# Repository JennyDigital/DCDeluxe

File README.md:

## It's a door chime board, but programmable.

It can literally sound however you want, but the source-code (unfinished) is provided to get you up-and-runninng.

Have you wondered why there's four DIP switches?.. Coming soon:  A melody playing feature!

...also, let me apologise for the ugly appearance of the CubeMX generated portions of the code, the tool generates ugly code and re-generates it with each re-generated change.  You can tidy it, but it'll just go back to ugly each time.

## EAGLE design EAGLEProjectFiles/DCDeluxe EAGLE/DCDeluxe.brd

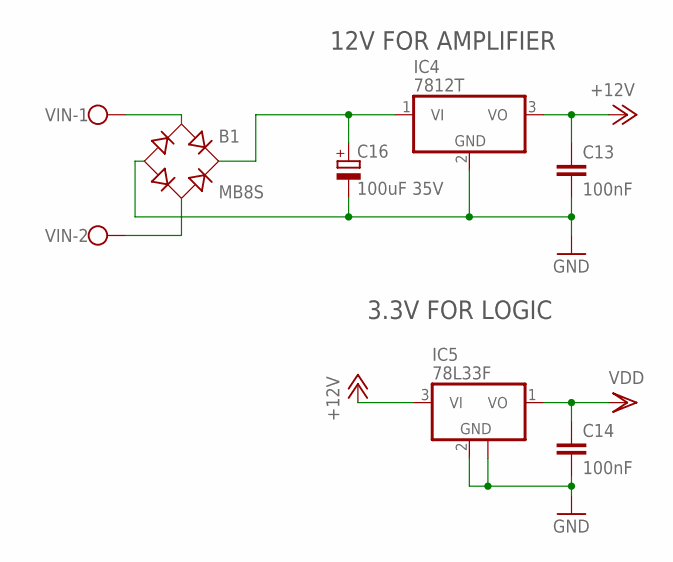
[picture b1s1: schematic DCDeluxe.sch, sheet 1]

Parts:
B1: MB8S; SOIC-4
C13, C14: 100nF; C0603
C16: 100uF 35V; 153CLV-0807
IC4: 7812T; TO220H
IC5: 78L33F; SOT89
VIN: W237-102

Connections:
+12V: C13.1, IC4.3 (VO), IC5.3 (VI); also elsewhere on the board
GND: B1.-, C13.2, C14.2, C16.-, IC4.2 (GND), IC5.2 (GND), IC5.2@1 (GND); also elsewhere on the board
VDD: C14.1, IC5.1 (VO); also elsewhere on the board
VIN1: B1.~1 (AC1), VIN.1; also elsewhere on the board
VIN2: B1.~2 (AC2), VIN.2; also elsewhere on the board
VIN+: B1.+, C16.+, IC4.1 (VI)

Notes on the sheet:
12V FOR AMPLIFIER
3.3V FOR LOGIC

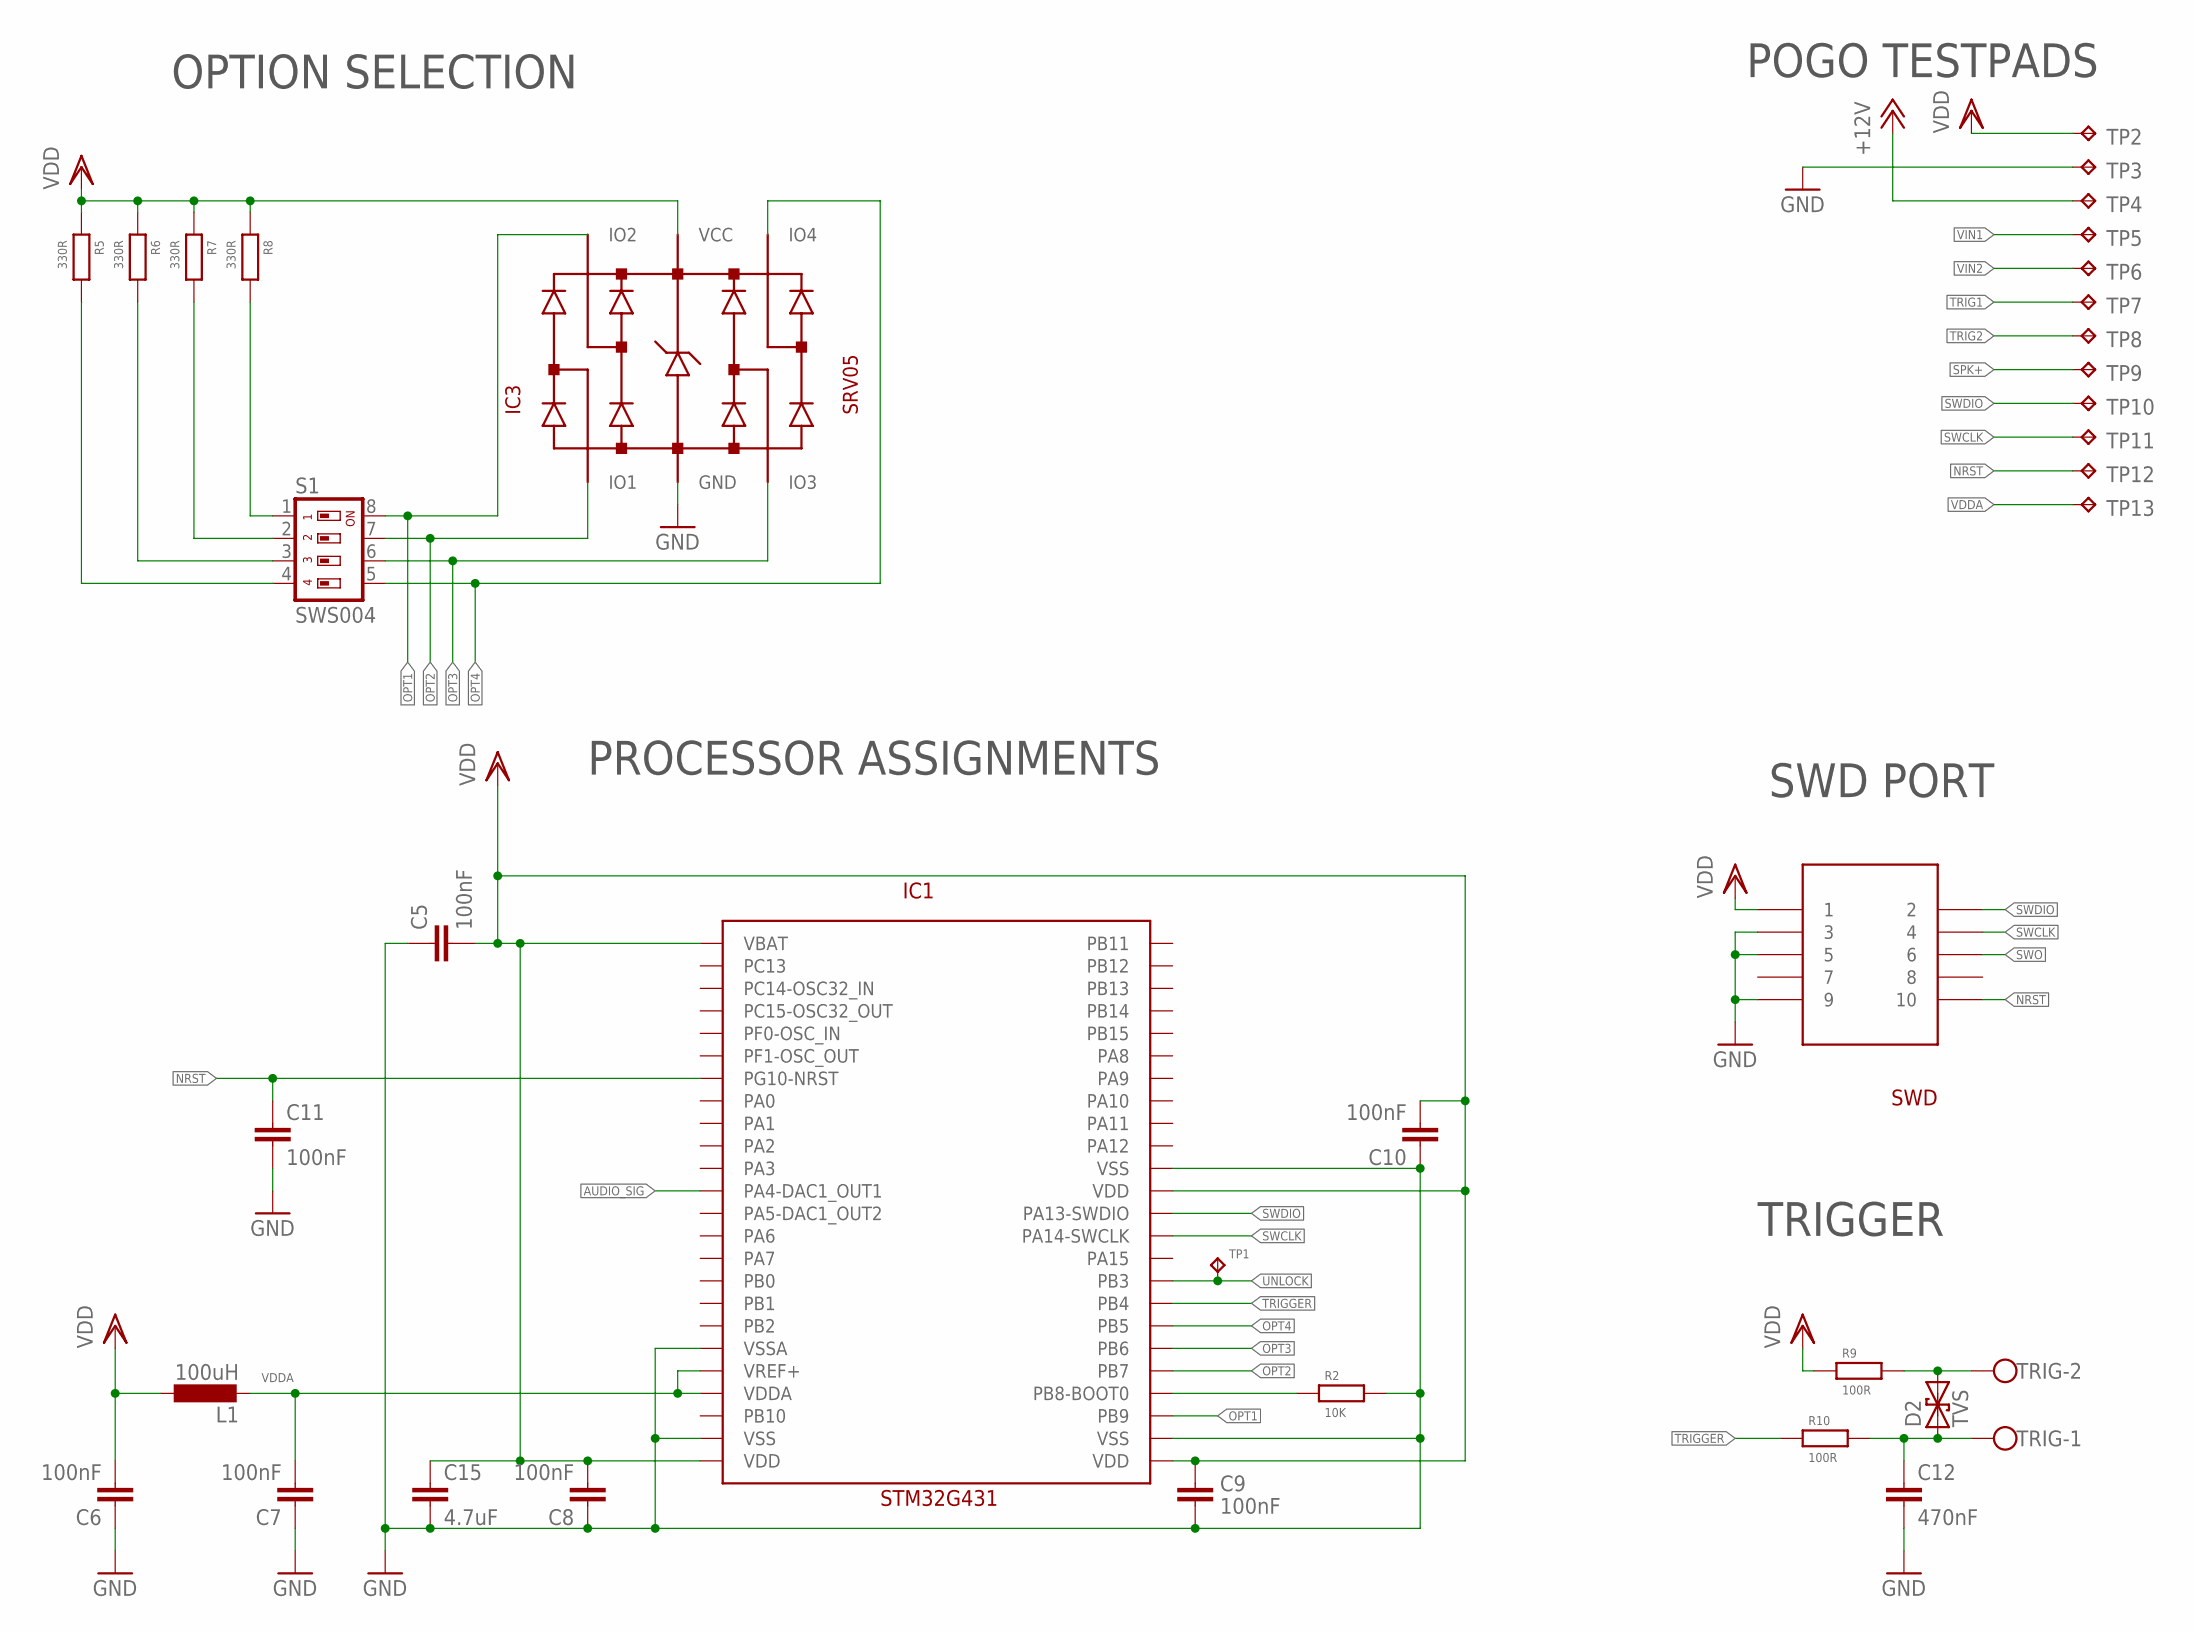
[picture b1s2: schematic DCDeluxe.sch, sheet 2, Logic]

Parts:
C5, C6, C7, C8, C9, C10, C11: 100nF; C0603
C12: 470nF; C0603
C15: 4.7uF; C0603
D2: TVS; SMA-DIODE
IC1: STM32G431; TQFP48
IC3: SRV05; TSOP-6
L1: 100uH; L3225M
R2: 10K; R0603
R5, R6, R7, R8: 330R; R0603
R9, R10: 100R; R0603
S1: SWS004; SMS-004
SWD: FTSH-105-01; FTSH-105-01-XXX-DV-K
TP1: TPTP12R; TP12R
TP2, TP3, TP4, TP5, TP6, TP7, TP8, TP9, TP10, TP11, TP12, TP13: TPTP20R; TP20R
TRIG: W237-102

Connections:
+12V: TP4.TP; also elsewhere on the board
AUDIO_SIG: IC1.PA4-DAC1_OUT1; also elsewhere on the board
BOOT0: IC1.PB8-BOOT0, R2.1
GND: C5.1, C6.1, C7.1, C8.1, C9.1, C10.1, C11.2, C12.2, C15.2, IC1.VSS@23 (VSS), IC1.VSS@35 (VSS), IC1.VSS@47 (VSS), IC1.VSSA, IC3.GND, R2.2, SWD.3, SWD.5, SWD.9, TP3.TP; also elsewhere on the board
unnamed: R8.2, S1.1
unnamed: R7.2, S1.2
unnamed: R6.2, S1.3
unnamed: R5.2, S1.4
NRST: C11.1, IC1.PG10-NRST, SWD.10, TP12.TP
OPT1: IC1.PB9, IC3.IO2, S1.8
OPT2: IC1.PB7, IC3.IO1, S1.7
OPT3: IC1.PB6, IC3.IO3, S1.6
OPT4: IC1.PB5, IC3.IO4, S1.5
SPK+: TP9.TP; also elsewhere on the board
SWCLK: IC1.PA14-SWCLK, SWD.4, TP11.TP
SWDIO: IC1.PA13-SWDIO, SWD.2, TP10.TP
SWO: SWD.6
TRIG1: C12.1, D2.A (1), R10.2, TP7.TP, TRIG.1
TRIG2: D2.C (2), R9.2, TP8.TP, TRIG.2
TRIGGER: IC1.PB4, R10.1
UNLOCK: IC1.PB3, TP1.TP
VDD: C5.2, C6.2, C8.2, C9.2, C10.2, C15.1, IC1.VBAT, IC1.VDD@24 (VDD), IC1.VDD@36 (VDD), IC1.VDD@48 (VDD), IC3.VCC, L1.1, R5.1, R6.1, R7.1, R8.1, R9.1, SWD.1, TP2.TP; also elsewhere on the board
VDDA: C7.2, IC1.VDDA, IC1.VREF+, L1.2, TP13.TP
VIN1: TP5.TP; also elsewhere on the board
VIN2: TP6.TP; also elsewhere on the board

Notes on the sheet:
OPTION SELECTION
PROCESSOR ASSIGNMENTS
TRIGGER
SWD PORT
POGO TESTPADS

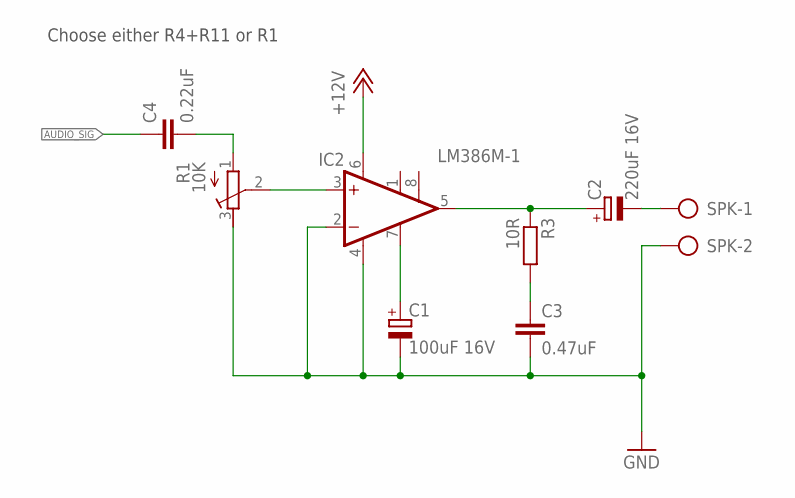
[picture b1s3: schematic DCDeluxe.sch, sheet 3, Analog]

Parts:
C1: 100uF 16V; 153CLV-0605
C2: 220uF 16V; 153CLV-0605
C3: 0.47uF; C0603
C4: 0.22uF; C0603
IC2: LM386M-1; SO08
R1: 10K; RTRIM3339P
R3: 10R; R0805
SPK: W237-102

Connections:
+12V: IC2.6 (VS); also elsewhere on the board
AUDIO_SIG: C4.1; also elsewhere on the board
GND: C1.-, C3.2, IC2.2 (-IN), IC2.4 (GND), R1.3 (A), SPK.2; also elsewhere on the board
unnamed: IC2.3 (+IN), R1.2 (S)
unnamed: C2.+, IC2.5 (OUT), R3.1
unnamed: C3.1, R3.2
unnamed: C4.2, R1.1 (E)
unnamed: C1.+, IC2.7 (BYPASS)
SPK+: C2.-, SPK.1; also elsewhere on the board

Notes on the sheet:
Choose either R4+R11 or R1

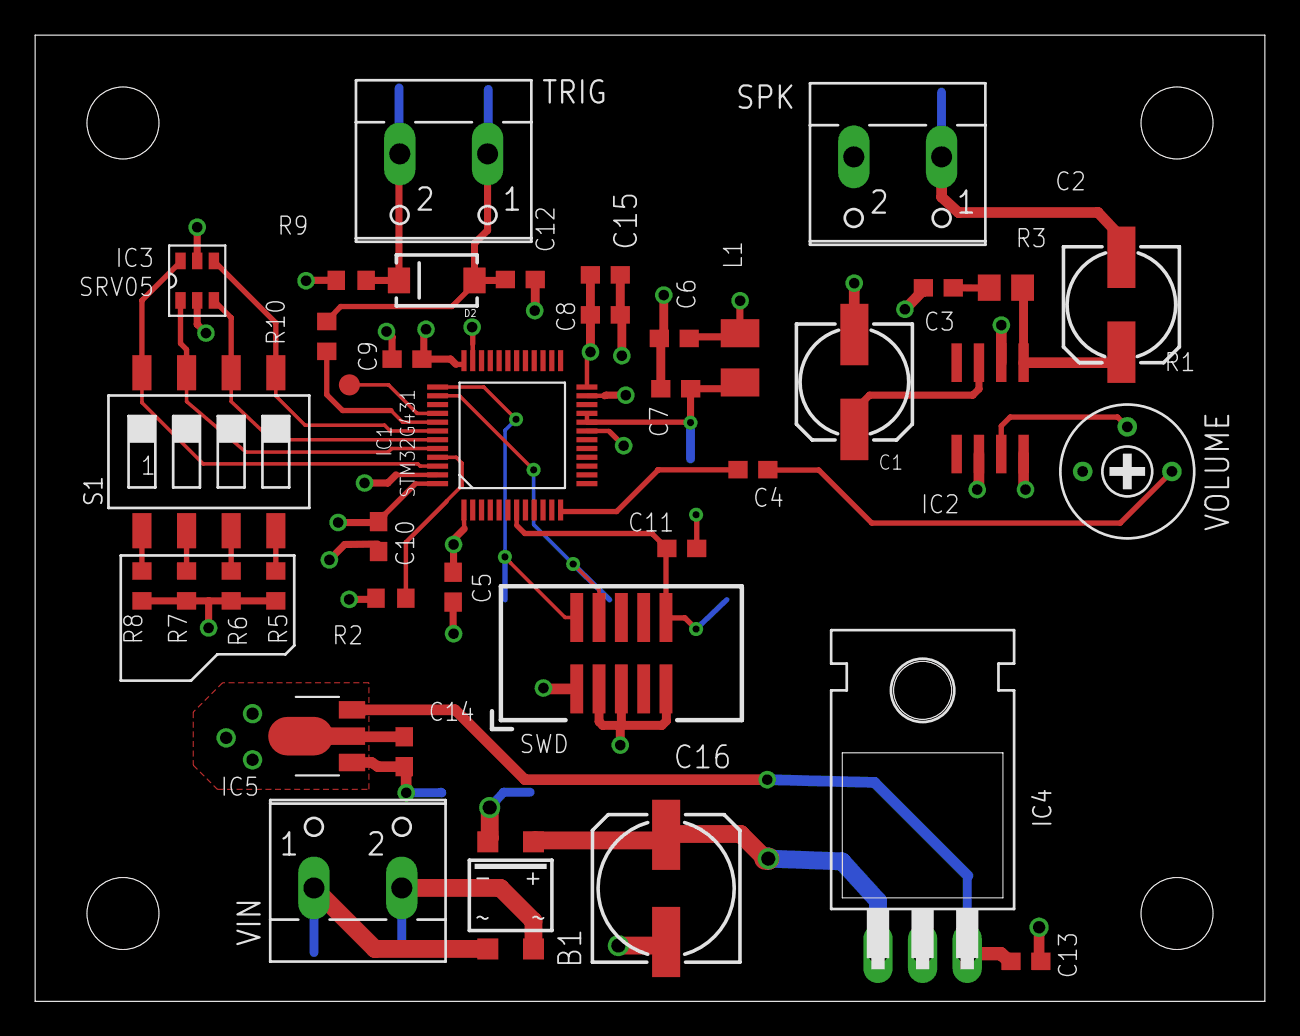
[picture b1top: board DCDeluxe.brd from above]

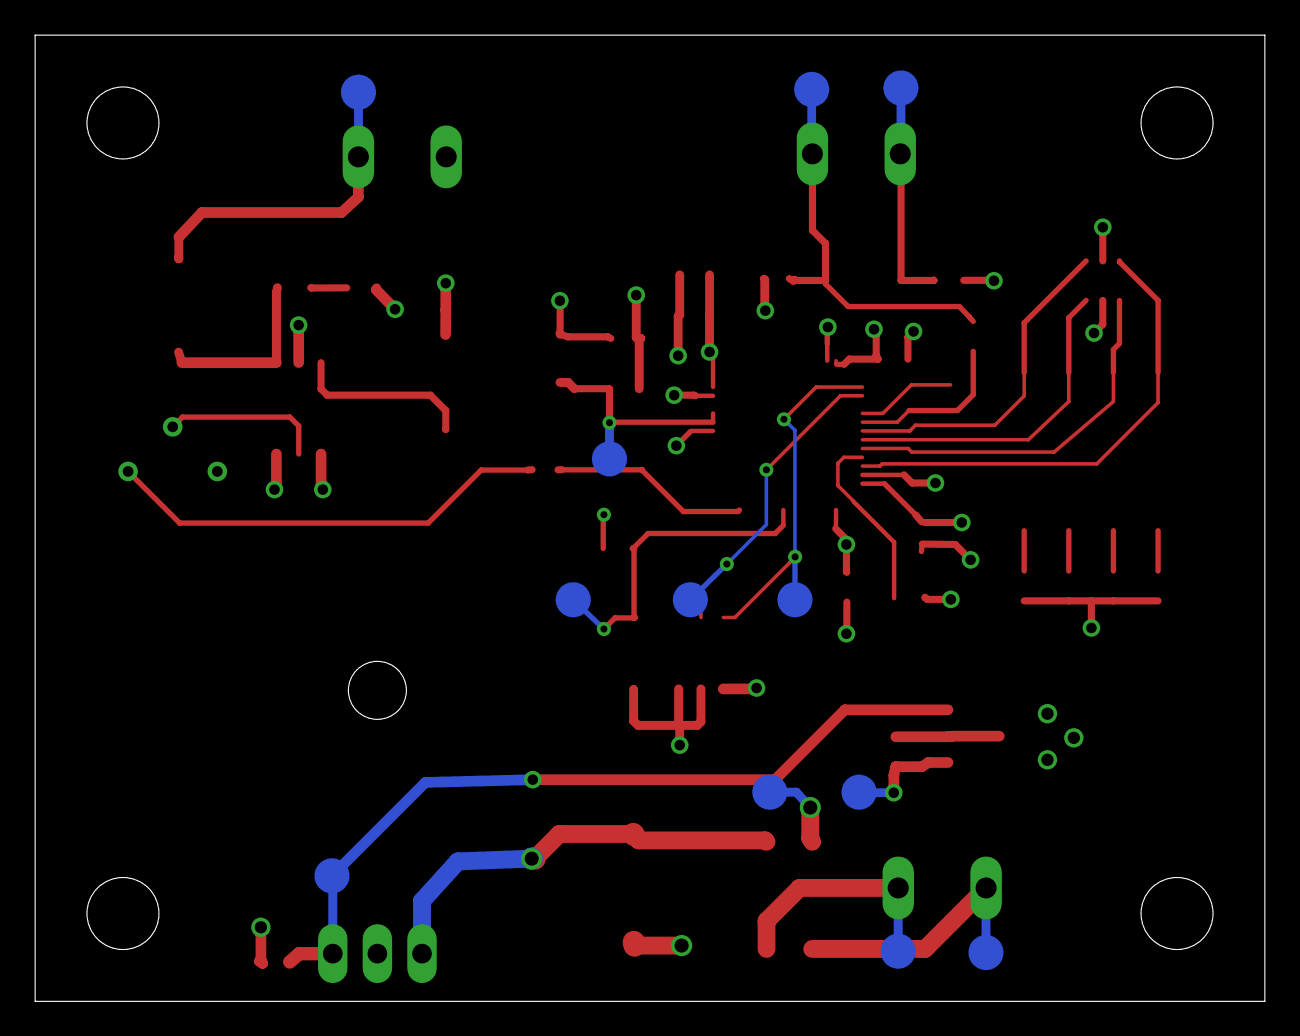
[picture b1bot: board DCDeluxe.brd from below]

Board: 4 copper layers, 70.0 x 55.0 mm, 51 parts (12 on the bottom side), 30 nets.

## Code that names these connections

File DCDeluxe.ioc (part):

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Mcu.Name=STM32G431C(6-8-B)Tx
Mcu.Package=LQFP48
Mcu.UserName=STM32G431C8Tx
PA13.Mode=Serial_Wire
PA13.Signal=SYS_JTMS-SWDIO
PA14.Mode=Serial_Wire
PA14.Signal=SYS_JTCK-SWCLK
PA4.GPIOParameters=GPIO_Label
PA4.GPIO_Label=AUDIO
PA4.Signal=COMP_DAC11_group
PB3.GPIOParameters=GPIO_PuPd,GPIO_Label
PB3.GPIO_Label=UNLOCK
PB3.GPIO_PuPd=GPIO_PULLDOWN
PB3.Signal=GPIO_Input
PB4.GPIOParameters=GPIO_PuPd,GPIO_Label
PB4.GPIO_Label=TRIGGER
PB4.GPIO_PuPd=GPIO_PULLDOWN
PB4.Signal=GPIO_Input
PB5.GPIOParameters=GPIO_PuPd,GPIO_Label
PB5.GPIO_Label=OPT4
PB5.GPIO_PuPd=GPIO_PULLDOWN
PB5.Signal=GPIO_Input
PB6.GPIOParameters=GPIO_PuPd,GPIO_Label
PB6.GPIO_Label=OPT3
PB6.GPIO_PuPd=GPIO_PULLDOWN
PB6.Signal=GPIO_Input
PB7.GPIOParameters=GPIO_PuPd,GPIO_Label
PB7.GPIO_Label=OPT2
PB7.GPIO_PuPd=GPIO_PULLDOWN
PB7.Signal=GPIO_Input
PB9.GPIOParameters=GPIO_PuPd,GPIO_Label
PB9.GPIO_Label=OPT1
PB9.GPIO_PuPd=GPIO_PULLDOWN
PB9.Signal=GPIO_Input
RCC.HSE_VALUE=8000000
RCC.SYSCLKFreq_VALUE=150000000
RCC.SYSCLKSource=RCC_SYSCLKSOURCE_PLLCLK
board=custom

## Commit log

2024-09-22 Initial commit.
2024-09-22 FIX: Tidied up the rubbish to make it more open source friendly
2024-09-22 FIX: Accidentally included an extra #, and also removed some unused variables.
2024-09-22 Added some comments, updated some chimeset data, and removed an unused variable
2024-09-23 FIX: Made adjustments to the code to reduce popping at start and settle the state to midpoint at end
2024-09-25 FEATURE: Reverse note sequence by setting switch 3
2024-09-25 Twiddled with the notes to my liking, I'm so fickle!
2024-09-25 TWEAKS: Updated PCB layout
2024-09-26 Tidied up a few leftovers. No functional change.
2024-09-26 Added google verification file
2024-09-26 Removed verification file, things clearly don't work this way
2024-09-26 Added more comments and made the code more readable
2024-09-26 Still trying to get my repo found
2024-09-26 Still failed to get google to find my repo.
2024-09-26 Adjustment: Moved the sine wave table to a const array in FLASH
2024-09-26 FIX: Remove warning from wave calculation with explicit cast
2024-09-26 Initial changes to support arbitrary score playback, not ready yet.
2024-09-26 Reoved unused defines
2024-09-26 FEATURE: Basic musical note playback is now possible with ACTUAL frequencies.
2024-09-27 Got a basic sequencer running with a simple scale. Also refactored for simplicitys sake
2024-09-27 Revert "FIX: Remove warning from wave calculation with explicit cast"
    This reverts commit 02eac132bfddab33ac2fe929af5cb5da98a03053.
    Having merge conflicts. I need to learn more about git!
2024-09-27 Removed a warning by explicit cast. This was reverted due to a mistake on my part, but is re-fixed now.
2024-09-27 FIX: Silly bug on my part!
2024-09-27 FIX: Set the starting position of a newly struck note to 2048 (halfway) to reduce start of note clicks.
    FIX: explicitly cast the chosen score array as (float *) to remove warning.
2024-10-07 FIX: Remove unncessary HAL_DAC_MspInit from main. FIX: Added a small delay to the start to allow the circuit to stabilise before chiming.
2024-10-07 FIX: Reduce the clickiness at startup by rearranging the initialisation of the DAC so that the DAC starts after the delay.
2024-10-07 FEATURE: Added another option to the sounds

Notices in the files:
parts and their libraries:
SparkFun-DiscreteSemi: Licensing: CC v3.0 Share-Alike You are welcome to use this library for commercial purposes.
